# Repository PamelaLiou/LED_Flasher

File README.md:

LED_Flasher
===========

Eagle Files for LED jewelry project

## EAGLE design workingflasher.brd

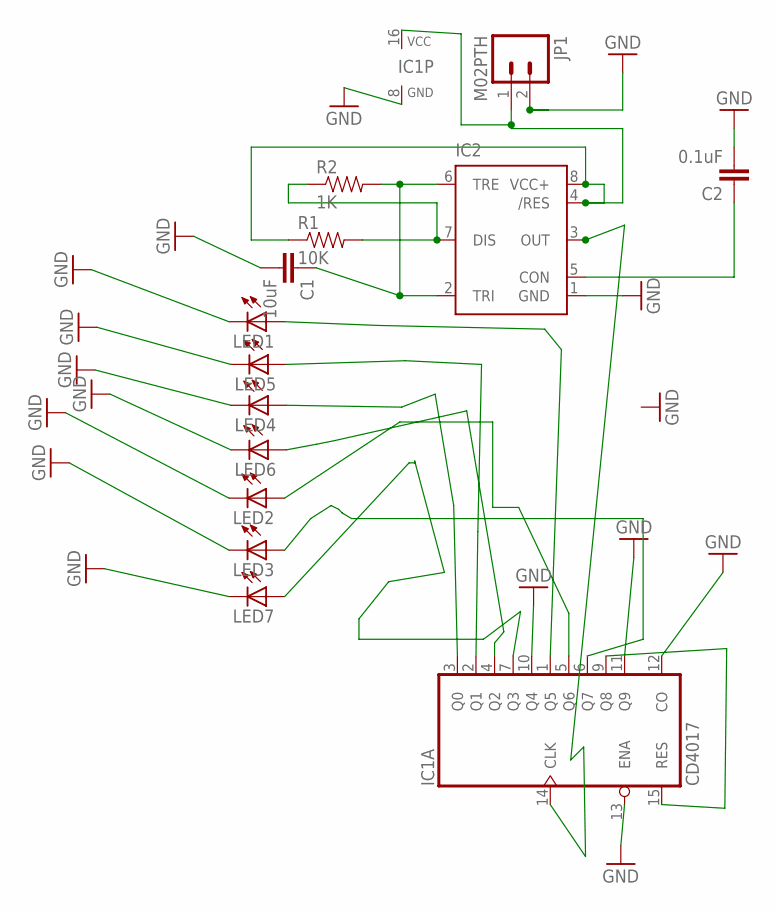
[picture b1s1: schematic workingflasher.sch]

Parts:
C1: 10uF; 1210
C2: 0.1uF; 0603-CAP
IC1: CD4017; DIL16
IC2: NE555D; SO08
JP1: M02PTH; 1X02
LED1, LED2, LED3, LED4, LED5, LED6, LED7: LED1206; LED-1206
R1: 10K; 0603
R2: 1K; 0603

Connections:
GND: C1.2, C2.2, IC1.8 (GND), IC1.10 (Q4), IC1.11 (Q9), IC1.12 (CO), IC1.13 (ENA), IC2.1 (GND), JP1.2, LED1.C, LED2.C, LED3.C, LED4.C, LED5.C, LED6.C, LED7.C
unnamed: IC1.1 (Q5), LED1.A
unnamed: IC1.5 (Q6), LED2.A
unnamed: IC1.9 (Q8), IC1.15 (RES)
unnamed: IC1.7 (Q3), LED7.A
unnamed: IC1.3 (Q0), LED4.A
unnamed: IC1.4 (Q2), LED6.A
unnamed: IC1.2 (Q1), LED5.A
unnamed: C2.1, IC2.5 (CON)
unnamed: C1.1, IC2.2 (TRI), IC2.6 (TRE), R2.2
unnamed: IC1.16 (VCC), IC2.4 (/RES), IC2.8 (VCC+), JP1.1, R1.1
unnamed: IC2.7 (DIS), R1.2, R2.1
unnamed: IC1.14 (CLK), IC2.3 (OUT)
unnamed: IC1.6 (Q7), LED3.A

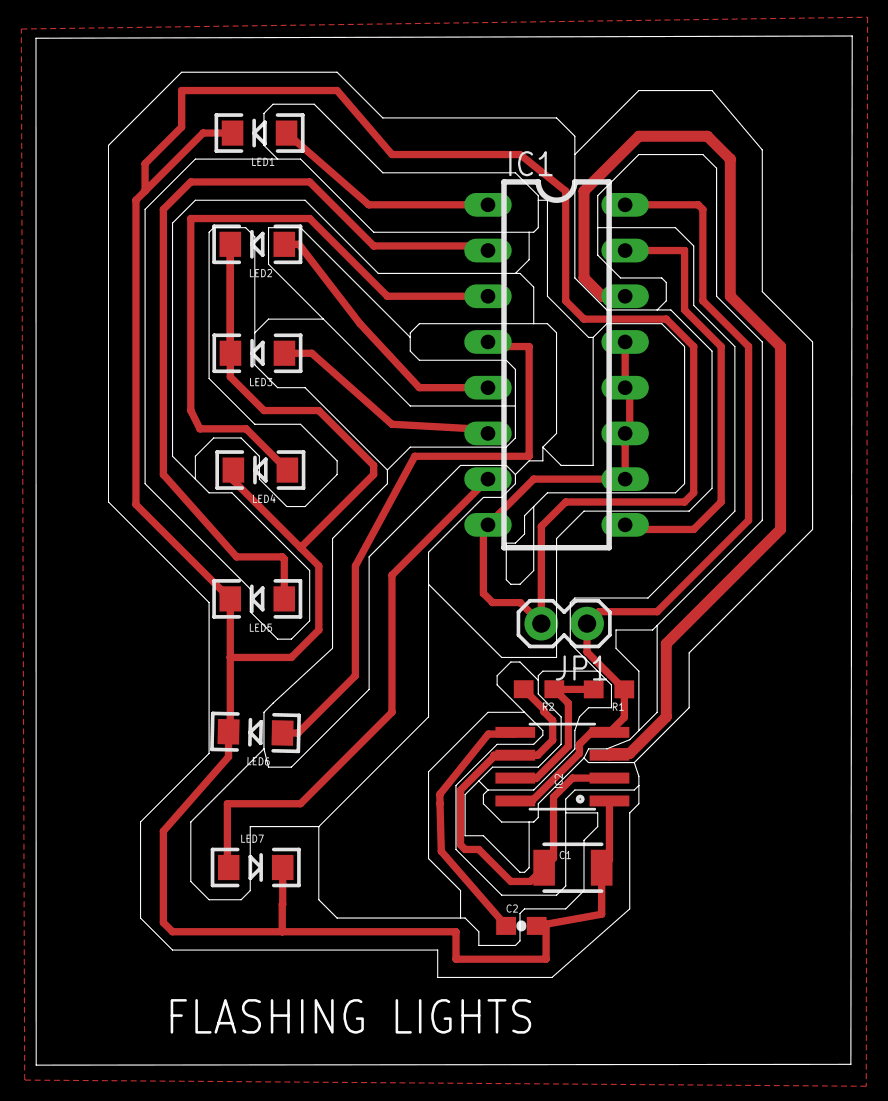
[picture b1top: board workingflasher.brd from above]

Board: 2 copper layers, 45.3 x 57.2 mm, 14 parts (0 on the bottom side), 14 nets.

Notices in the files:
parts and their libraries:
SparkFun-Capacitors: Licensing: CC v3.0 Share-Alike You are welcome to use this library for commercial purposes.
SparkFun-Resistors: Licensing: Creative Commons ShareAlike 4.0 International - https://creativecommons.org/licenses/by-sa/4.0
